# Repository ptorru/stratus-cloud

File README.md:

# stratus-cloud
Trying to build cloud like services in a home cluster. Stratus/strato: flat/layered and smooth.

The goal is to have a collection of Applications that can be deployed in one, or many, clusters running on multiple machines in a network. For example:

* A small cluster with color screens to draw funky graphics on.
* A small cluster of Raspberry Pi zero's to get ambient data.

These are two separate applications, and they could run on the same cluster, or in different logical clusters using the same hardware, or run on a separate cluster with different underlying hardware.

# Why are we doing this?

Educational purposes, and to finally get some of the HW I have at home to do something useful!

# Project structure

This repo will be divided mostly between Applications and Infrastructure code.

Inside each folder there will be a collection of self-contained items or tools that have will have a given purpose.

* Application: Holds application specific code. New app? create a new folder!
* Infrastructure: Holds code to provision/deploy a cluster where applications can be run. Want a new cluster? want a remixed version? create a new folder!

# Environment
If targetting a Raspberry Pi Zero, care must be taken as the usual gcc/linker available under the tag *arm-linux-gnueabihf* produces code that is compatible with armv7 in reality, not with armv6 for the Pi Zero. Quick solution would be to checkout the tools repo, from the official Raspberry Pi GitHub area, and set environment to point to it, eg:

```bash
git clone git@github.com:raspberrypi/tools.git raspberrypi_tools

cd project_folder
cargo clean
# assuming the checkout was one in the home directory.
export PATH="$HOME/raspberrypi_tools/arm-bcm2708/arm-linux-gnueabihf/bin:$PATH"
cargo build --target arm-unknown-linux-gnueabihf
```
This will yield a viable binary that can then be copied onto the Pi Zero and executed successfully.

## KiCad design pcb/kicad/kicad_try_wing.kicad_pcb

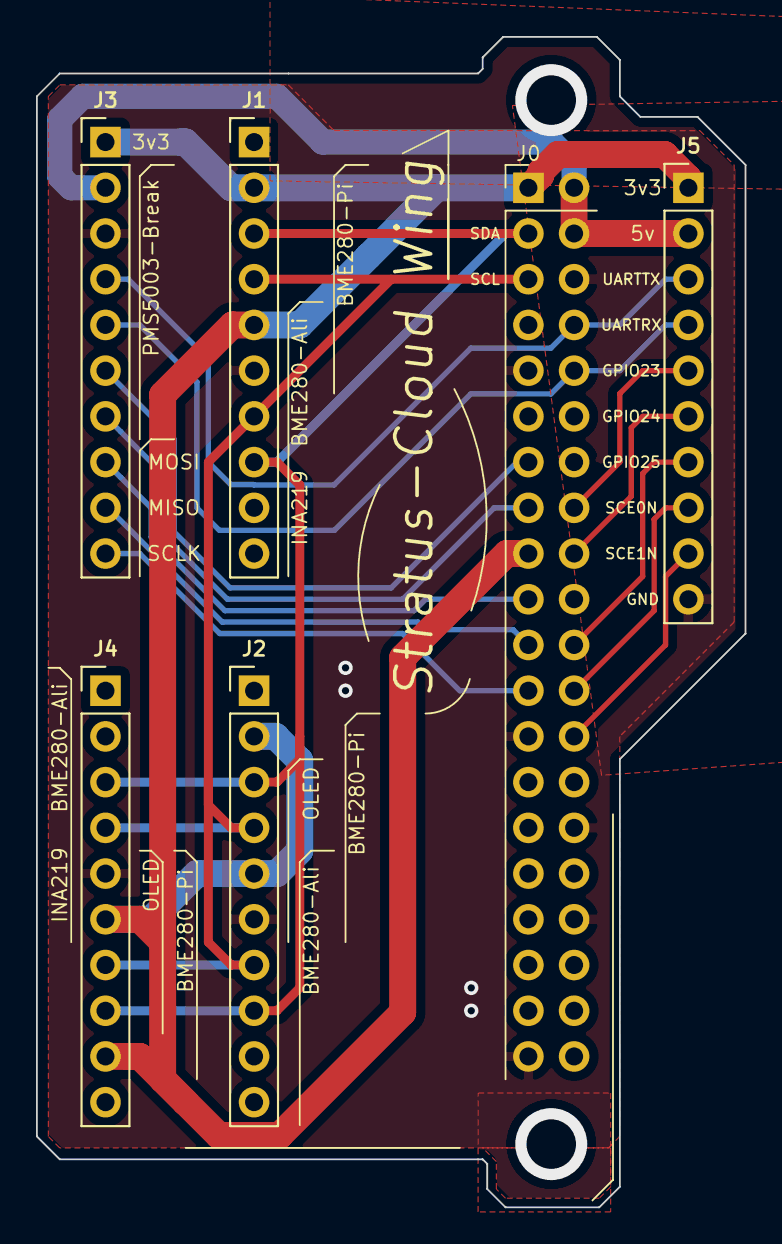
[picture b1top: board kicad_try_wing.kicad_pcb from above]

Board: 2 copper layers, 39.4 x 65.0 mm, 6 parts (1 on the bottom side), 17 nets.

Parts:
J0: Conn_02x40_Odd_Even; PinSocket_2x20_P2.54mm_Vertical
J1: Conn_01x08; PinHeader_1x10_P2.54mm_Vertical
J2, J3, J4, J5: Conn_01x10; PinHeader_1x10_P2.54mm_Vertical

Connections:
+3V3: J0.1, J0.17, J1.2, J1.5, J2.2, J2.5, J3.1, J4.6, J4.9, J5.1
+5V: J0.2, J0.4, J3.2, J5.2
GND: J0.6, J0.9, J0.14, J0.20, J0.25, J0.30, J0.34, J0.39, J1.6, J2.6, J3.3, J4.5, J5.10
GPIO9-MISO: J0.21, J3.9
GPIO10-MOSI: J0.19, J3.8
GPIO11-SCLK: J0.23, J3.10
GPIO22-EN: J0.15, J3.7
GPIO27-RESET: J0.13, J3.6
unnamed: J0.16, J5.5
unnamed: J0.18, J5.6
unnamed: J0.22, J5.7
unnamed: J0.24, J5.8
unnamed: J0.26, J5.9
SCL: J0.5, J1.4, J1.7, J2.4, J2.7, J4.4, J4.7
SDA: J0.3, J1.3, J1.8, J2.3, J2.8, J4.3, J4.8
URX: J0.10, J3.5, J5.4
UTX: J0.8, J3.4, J5.3

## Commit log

2021-09-14 Adding first app to repo
2021-09-19 Adding notes and config to target RPi Zero
2021-09-19 Adding new line at end of file
2021-09-28 Changed ip address to allow connection.
2021-10-09 Adding the ambient app
2021-10-12 Added missing file
2021-10-12 Adding files looking for help
2021-10-13 Added support for the oled display. Fixed build.sh.
2021-10-25 All integrated and working.
2021-10-25 Added data to proto, done display.
2021-10-25 Added some prep inspiration notes on nomad.
2021-10-26 Adding more references on using nomad.
2021-10-27 First working version of prometheus exporter.
2021-10-27 Updated gitignore
2021-10-27 Version getting data from i2c.
2021-11-03 Checkpoint, trying to x-compile for pizero
2021-11-03 Added wing pcb files
2021-11-03 Added missing project file
2021-11-03 First version of nomad job def for ambient_prom
